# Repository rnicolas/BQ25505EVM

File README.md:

# BQ25570EVM

The working files of this component need [this library](https://github.com/rnicolas/Battery_Management) to be added into your library.

If you just want the gerber files to build this PCB on your own, just download this [zip](https://github.com/rnicolas/BQ25570EVM/blob/master/output/bq25570evm.zip?raw=true). Board is still on development and some tests are still needed, so use it at your own risk.

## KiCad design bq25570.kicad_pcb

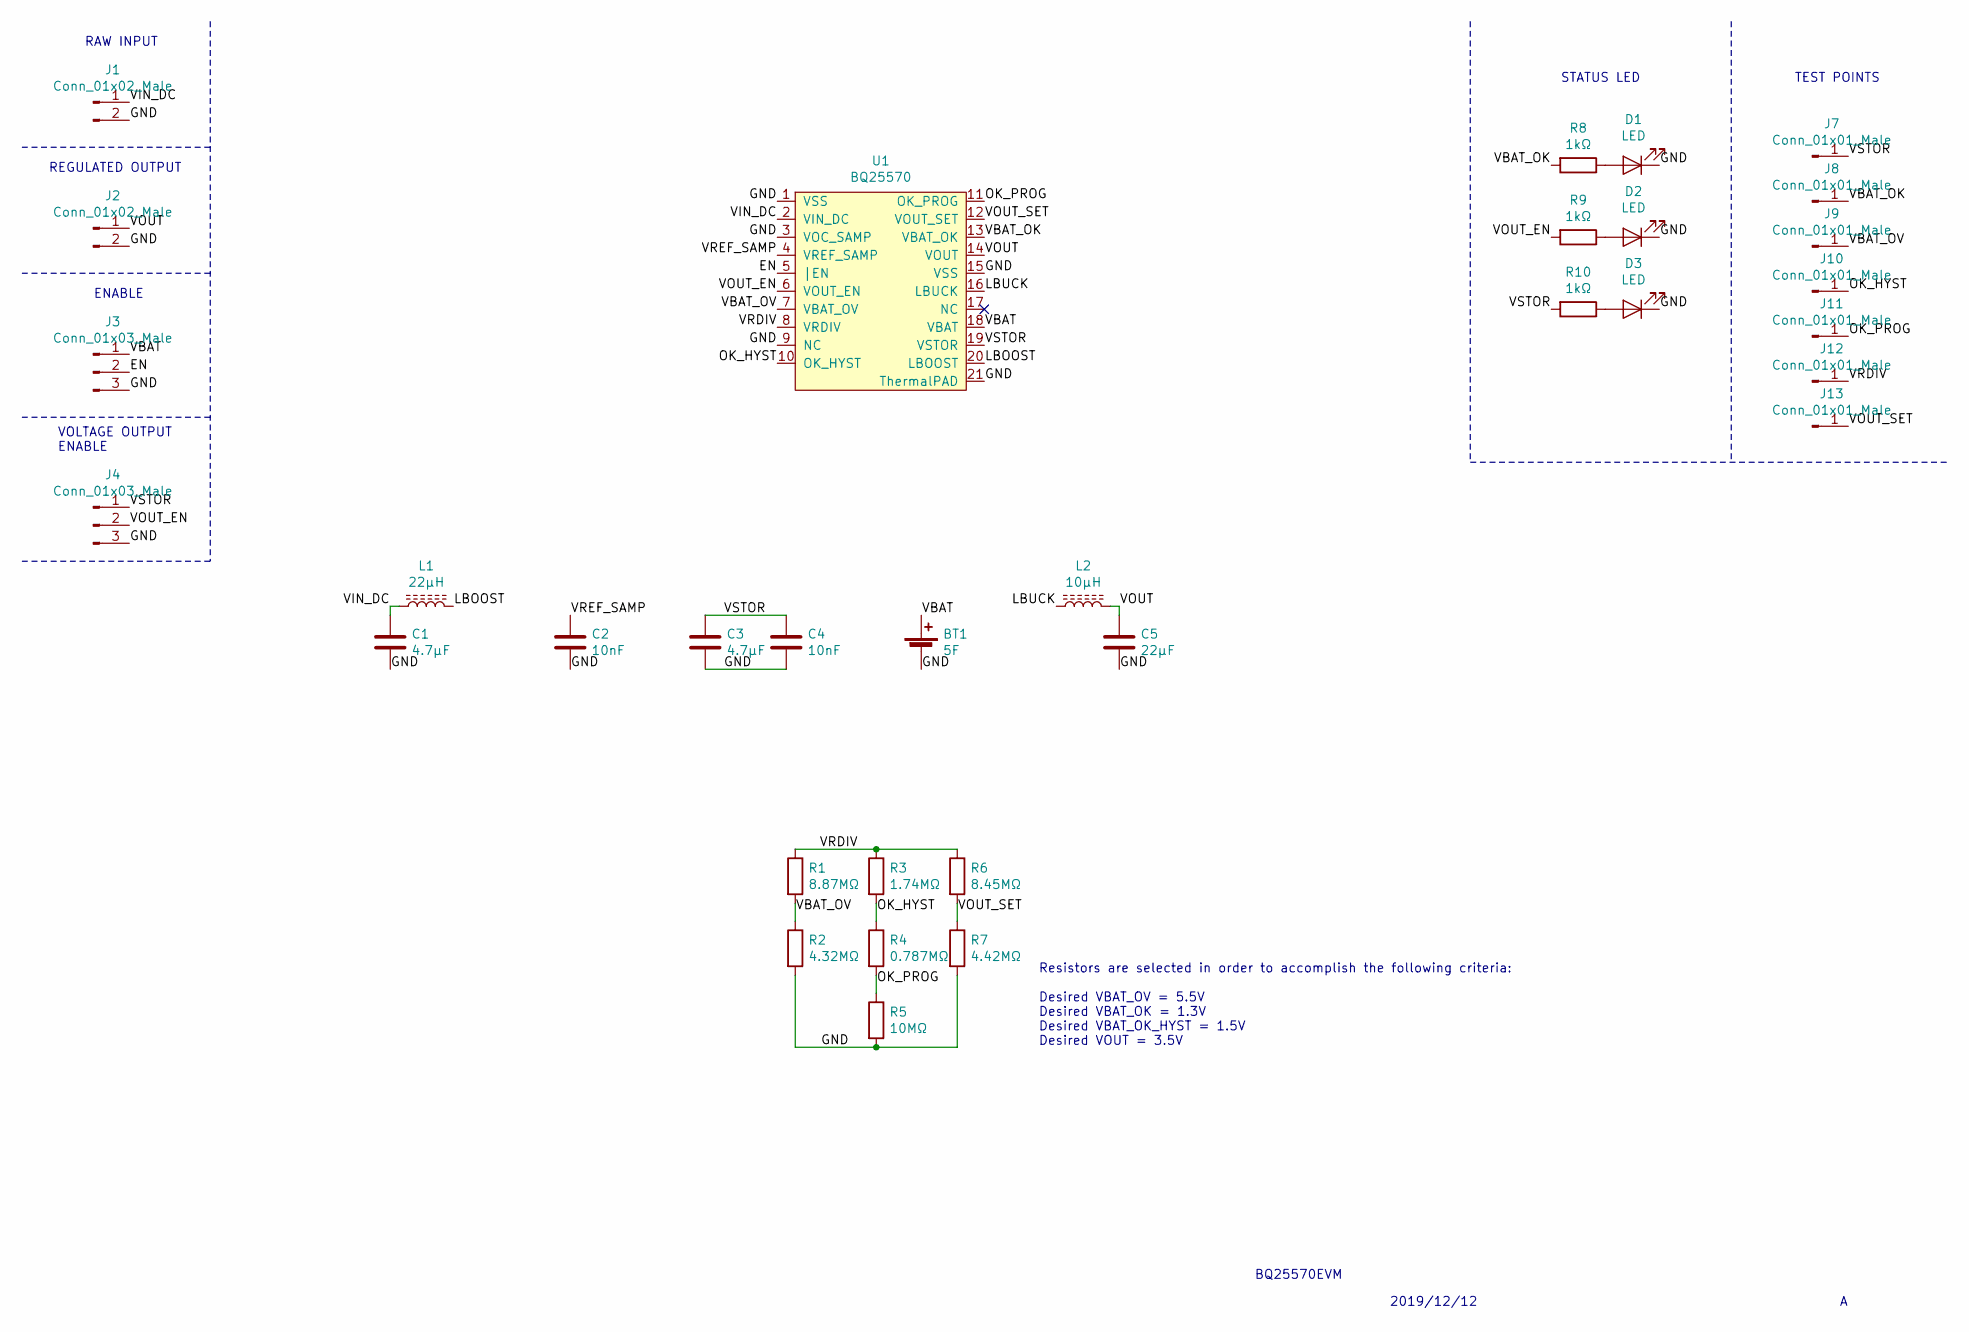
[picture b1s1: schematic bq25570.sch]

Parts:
BT1: 5F; PinHeader_1x02_P5.50mm_Vertical
C1, C3: 4.7μF; C_0805_2012Metric_Pad1.15x1.40mm_HandSolder
C2, C4: 10nF; C_0805_2012Metric_Pad1.15x1.40mm_HandSolder
C5: 22μF; C_0805_2012Metric_Pad1.15x1.40mm_HandSolder
D1, D2, D3: LED; LED_0805_2012Metric_Pad1.15x1.40mm_HandSolder
J1, J2: Conn_01x02_Male; PinHeader_1x02_P2.54mm_Vertical
J3, J4: Conn_01x03_Male; PinHeader_1x03_P2.54mm_Vertical
J7, J8, J9, J10, J11, J12, J13: Conn_01x01_Male; PinHeader_1x01_P2.54mm_Vertical
L1: 22μH; L_Coilcraft_LPS4018
L2: 10μH; L_Coilcraft_LPS4018
R1: 8.87MΩ; R_0603_1608Metric_Pad1.05x0.95mm_HandSolder
R2: 4.32MΩ; R_0805_2012Metric_Pad1.15x1.40mm_HandSolder
R3: 1.74MΩ; R_0805_2012Metric_Pad1.15x1.40mm_HandSolder
R4: 0.787MΩ; R_0805_2012Metric_Pad1.15x1.40mm_HandSolder
R5: 10MΩ; R_0805_2012Metric_Pad1.15x1.40mm_HandSolder
R6: 8.45MΩ; R_0805_2012Metric_Pad1.15x1.40mm_HandSolder
R7: 4.42MΩ; R_0805_2012Metric_Pad1.15x1.40mm_HandSolder
R8, R9, R10: 1kΩ; R_0805_2012Metric_Pad1.15x1.40mm_HandSolder
U1: BQ25570; Texas_RGR_S-PVQFN-N20_EP2.05x2.05mm_ThermalVias

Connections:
/EN: J3.2, U1.5 (|EN)
/GND: BT1.2 (-), C1.2, C2.2, C3.2, C4.2, C5.2, D1.1 (K), D2.1 (K), D3.1 (K), J1.2, J2.2, J3.3, J4.3, R2.2, R5.2, R7.2, U1.1 (VSS), U1.3 (VOC_SAMP), U1.9 (NC), U1.15 (VSS), U1.21 (ThermalPAD)
/LBOOST: L1.2, U1.20 (LBOOST)
/LBUCK: L2.1, U1.16 (LBUCK)
/OK_HYST: J10.1, R3.2, R4.1, U1.10 (OK_HYST)
/OK_PROG: J11.1, R4.2, R5.1, U1.11 (OK_PROG)
/VBAT: BT1.1 (+), J3.1, U1.18 (VBAT)
/VBAT_OK: J8.1, R8.2, U1.13 (VBAT_OK)
/VBAT_OV: J9.1, R1.2, R2.1, U1.7 (VBAT_OV)
/VIN_DC: C1.1, J1.1, L1.1, U1.2 (VIN_DC)
/VOUT: C5.1, J2.1, L2.2, U1.14 (VOUT)
/VOUT_EN: J4.2, R9.2, U1.6 (VOUT_EN)
/VOUT_SET: J13.1, R6.2, R7.1, U1.12 (VOUT_SET)
/VRDIV: J12.1, R1.1, R3.1, R6.1, U1.8 (VRDIV)
/VREF_SAMP: C2.1, U1.4 (VREF_SAMP)
/VSTOR: C3.1, C4.1, J4.1, J7.1, R10.2, U1.19 (VSTOR)
unnamed: D1.2 (A), R8.1
unnamed: D2.2 (A), R9.1
unnamed: D3.2 (A), R10.1

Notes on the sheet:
TEST POINTS
BQ25570EVM
2019/12/12
STATUS LED
RAW INPUT
REGULATED OUTPUT
Resistors are selected in order to accomplish the following criteria: Desired VBAT_OV = 5.5V Desired VBAT_OK = 1.3V Desired VBAT_OK_HYST = 1.5V Desired VOUT = 3.5V
ENABLE
VOLTAGE OUTPUT ENABLE

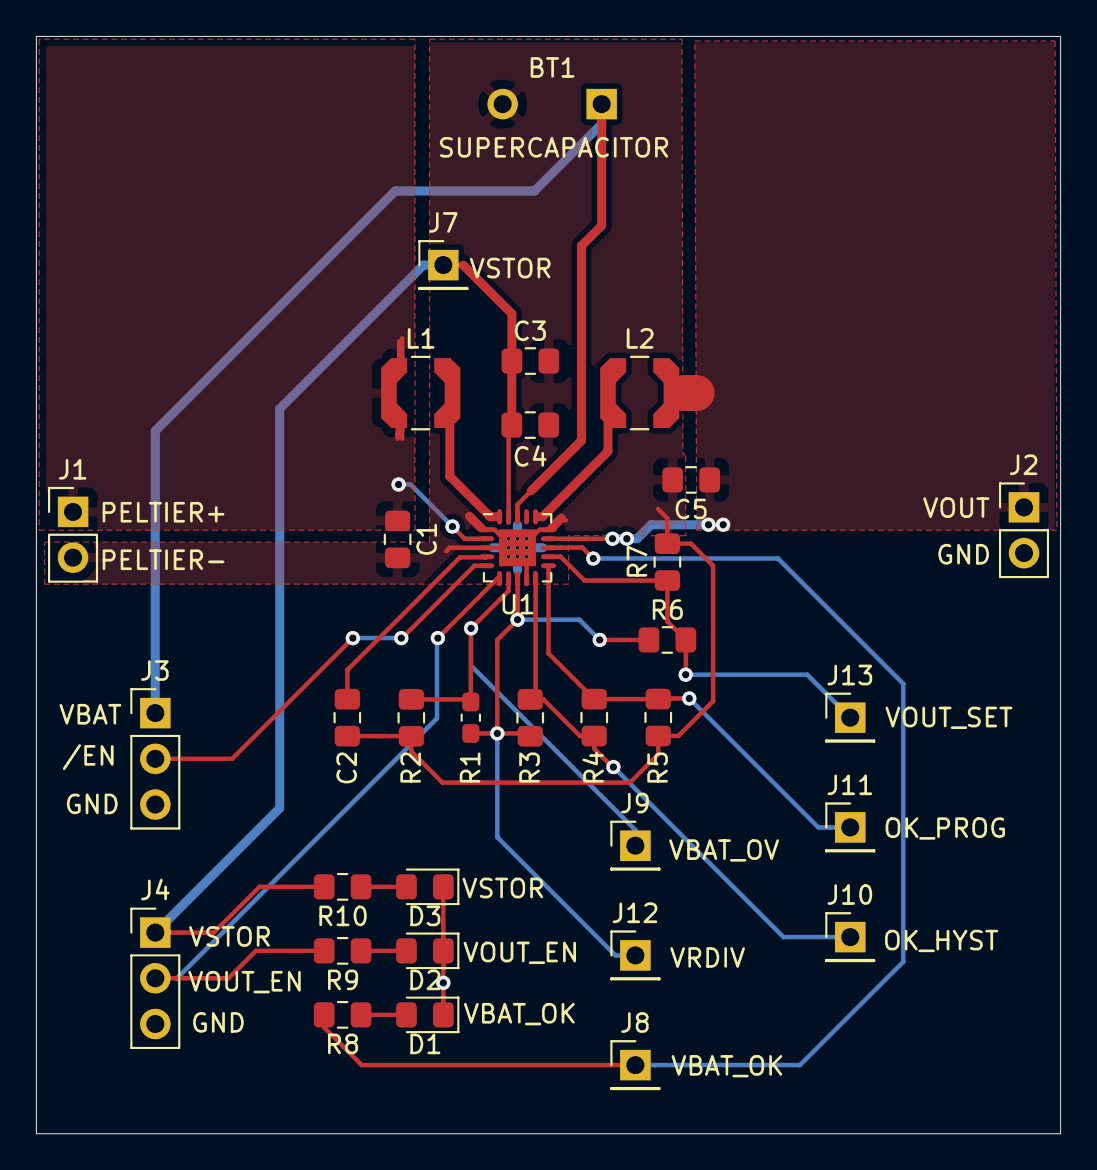
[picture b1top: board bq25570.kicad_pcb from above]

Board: 2 copper layers, 56.9 x 61.0 mm, 33 parts (0 on the bottom side), 19 nets.

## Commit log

2019-12-12 Referencing other repository containing the schematic and footprint of BQ25505
2019-12-12 Rearranged some elements on the schematic file
2019-12-13 Added datasheets
2019-12-16 It's not a BQ25505, it's a BQ25570
2019-12-17 Restarted from zero, resistors must be calculated
2019-12-17 Gitignore added
2019-12-17 Spreadsheet adapted to 6V supercap
2019-12-18 Schematic done
2019-12-19 Schematic finished, components added, PCB design started
2019-12-20 PCB started
2020-01-07 PCB layout done. Checking needed
2020-01-07 sch-bak deleted
2020-01-10 Footprint bt changed
2020-01-20 Gerber files added in output folder
2020-02-04 BQ25570 footprint updated
2020-02-19 0.01uF renamed to 10nF
2020-02-19 Cleaning the repo
2020-02-19 bom file deleted
2020-02-19 README updated
2020-02-19 bq25570 datasheet added
2020-02-20 Removing older files
2020-02-20 Gerber files modified to include silkscreen between IC pads
2020-02-21 fp-info-cache deleted
2020-02-21 Added gerber files to the repository
